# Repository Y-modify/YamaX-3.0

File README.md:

# YamaX 3.0

This is the software of humanoid robot named "YamaX 3.0"
The humanoid uses the original board with ESP8266.
This repository contains 3D Models, EAGLE files, and Arduino sketch.

Detailed information about this robot can be found in the following page: 

- [Y-modify](http://www.y-modify.org)
- [Y-modify Blog](http://blog.y-modify.org)

## Directory Structure

```
.
├── Designs
│   ├── AXBoard
│   │   ├── AX-03r	#EAGLE PCB file
│   │   └── Legacy	#Legacy Board (AX-03)
│   └── Model	#3D model of YamaX
├── Docs	#Document about the history of YamaX
└── Firmware
    └── AXBoard
        ├── AXTester	#Testing Program
        └── MCore	#Main Program
```

## Licence

These files are released under MIT Licence.
Please see `LICENCE`.

## Contact

You can comment on [our blog](http://blog.y-modify.org), or send e-mail to [info@y-modify.org](mailto:info@y-modify.org).

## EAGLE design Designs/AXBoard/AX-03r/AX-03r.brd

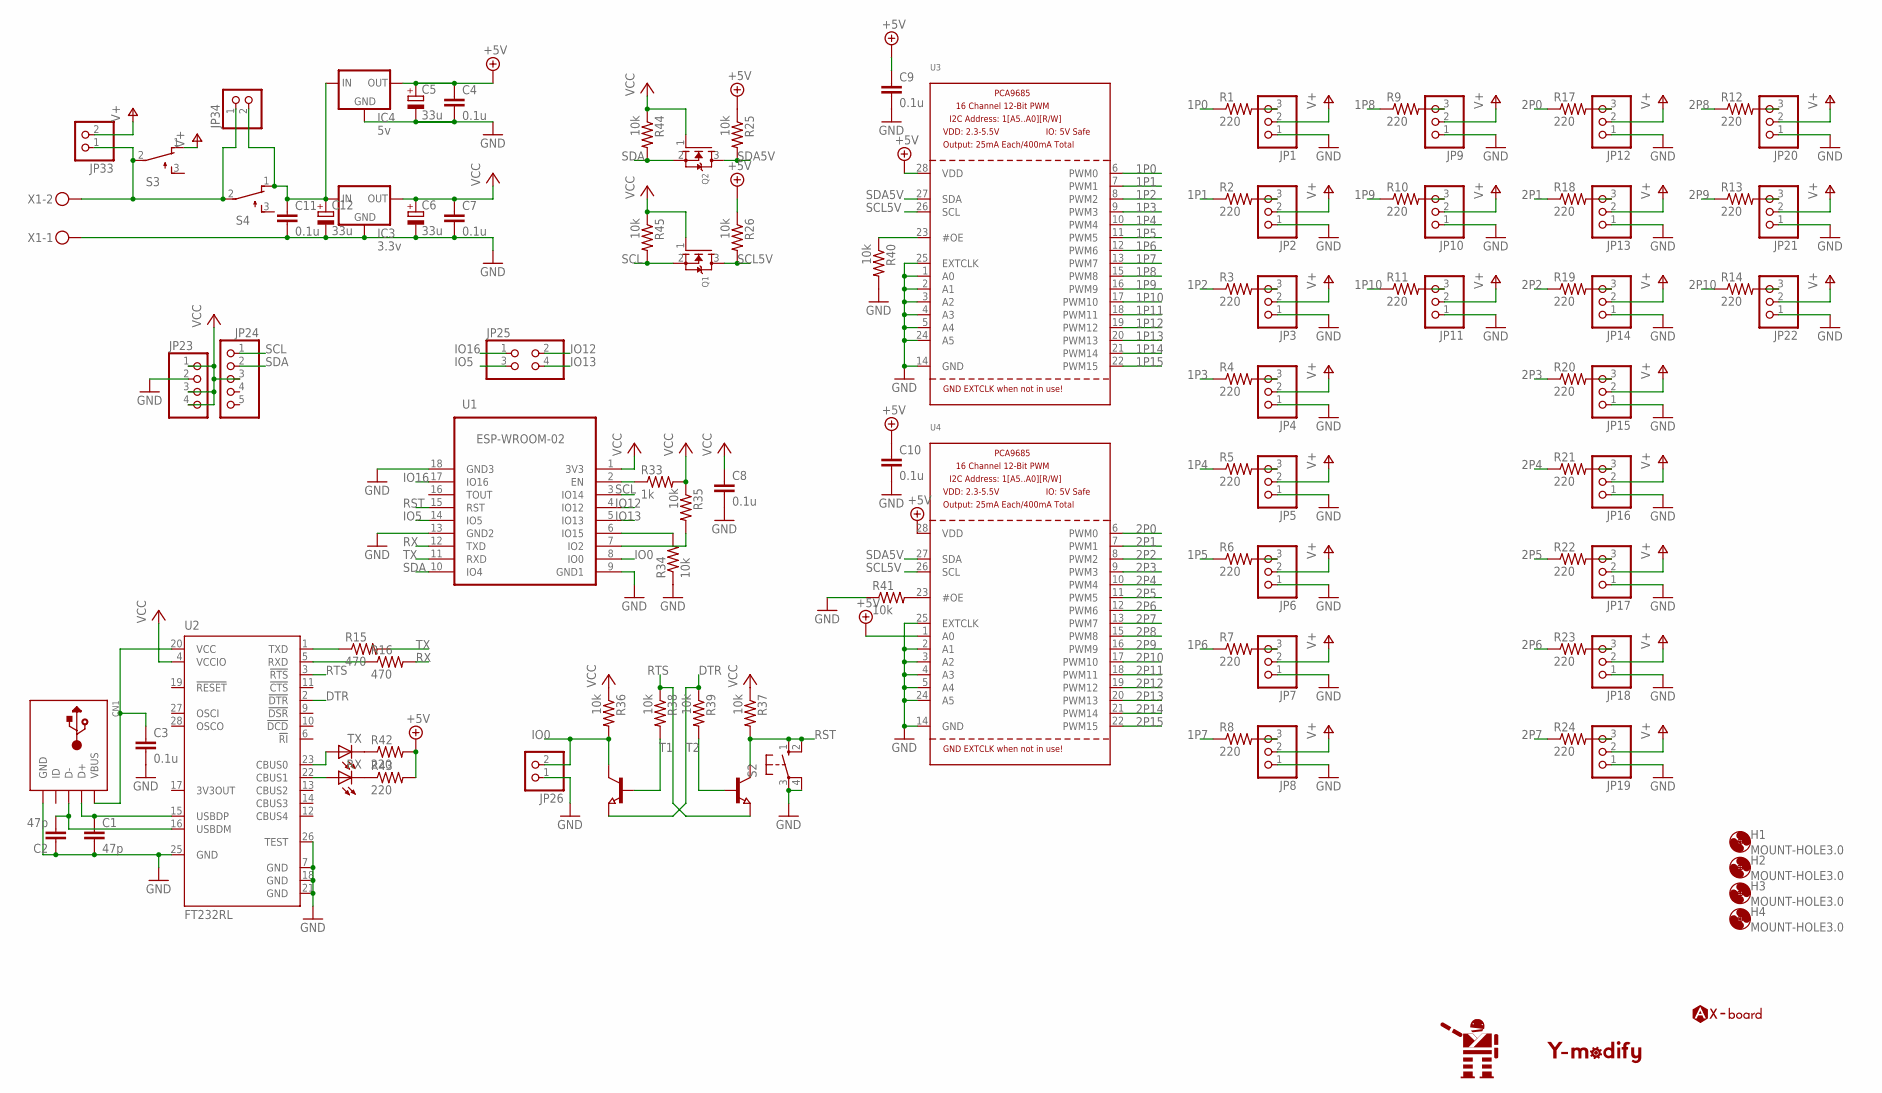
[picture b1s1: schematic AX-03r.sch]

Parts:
C1, C2: 47p; C025-025X050
C3, C4, C7, C8, C9, C10, C11: 0.1u; C025-025X050
C5, C6, C12: 33u; E2,5-6E
CN1: USBTHM; USB-MINIB-THM
H1, H2, H3, H4: MOUNT-HOLE3.0; 3,0
IC3: 3.3v; 78XXS
IC4: 5v; 78XXS
JP1, JP2, JP3, JP4, JP5, JP6, JP7, JP8, JP9, JP10, JP11, JP12, JP13, JP14, JP15, JP16, JP17, JP18, JP19, JP20, JP21, JP22: PINHD-1X3; 1X03
JP23: PINHD-1X4; 1X04
JP24: PINHD-1X5; 1X05
JP25: PINHD-2X2; 2X02
JP26, JP33, JP34: PINHD-1X2; 1X02
M1: MON
M2: Y-MODIFY
M3: AXBOARD
Q1, Q2: MOSFET-NWAVE; SOT23-W
R1, R2, R3, R4, R5, R6, R7, R8, R9, R10, R11, R12, R13, R14, R17, R18, R19, R20, R21, R22, R23, R24, R42, R43: 220; 0204V
R15, R16: 470; 0204V
R25, R26, R34, R35, R36, R37, R38, R39, R40, R41, R44, R45: 10k; 0204V
R33: 1k; 0204V
RX: LED3MM
S2: 10-XX; B3F-10XX
S3, S4: TL32PO; TL3XPO
T1, T2: NPN-TRANSISTOR_SOT23; SOT23
TX: LED3MM
U1: ESP-WROOM-02; FRONT-FACE
U2: FT232RL; SSOP28
U3, U4: PCA9685; TSSOP28
X1: MKDSN1,5/2-5,08

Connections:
1P0: R1.1, U3.6 (PWM0)
1P1: R2.1, U3.7 (PWM1)
1P2: R3.1, U3.8 (PWM2)
1P3: R4.1, U3.9 (PWM3)
1P4: R5.1, U3.10 (PWM4)
1P5: R6.1, U3.11 (PWM5)
1P6: R7.1, U3.12 (PWM6)
1P7: R8.1, U3.13 (PWM7)
1P8: R9.1, U3.15 (PWM8)
1P9: R10.1, U3.16 (PWM9)
1P10: R11.1, U3.17 (PWM10)
1P11: U3.18 (PWM11)
1P12: U3.19 (PWM12)
1P13: U3.20 (PWM13)
1P14: U3.21 (PWM14)
1P15: U3.22 (PWM15)
2P0: R17.1, U4.6 (PWM0)
2P1: R18.1, U4.7 (PWM1)
2P2: R19.1, U4.8 (PWM2)
2P3: R20.1, U4.9 (PWM3)
2P4: R21.1, U4.10 (PWM4)
2P5: R22.1, U4.11 (PWM5)
2P6: R23.1, U4.12 (PWM6)
2P7: R24.1, U4.13 (PWM7)
2P8: R12.1, U4.15 (PWM8)
2P9: R13.1, U4.16 (PWM9)
2P10: R14.1, U4.17 (PWM10)
2P11: U4.18 (PWM11)
2P12: U4.19 (PWM12)
2P13: U4.20 (PWM13)
2P14: U4.21 (PWM14)
2P15: U4.22 (PWM15)
+5V: C4.1, C5.+, C9.1, C10.1, IC4.OUT, R25.1, R26.1, R42.2, R43.2, U3.28 (VDD), U4.1 (A0), U4.28 (VDD)
DTR: R39.1, T1.2 (E), U2.2 (!DTR)
GND: C1.2, C2.1, C3.2, C4.2, C5.-, C6.-, C7.2, C8.2, C9.2, C10.2, C11.2, C12.-, CN1.GND, IC3.GND, IC4.GND, JP1.1, JP2.1, JP3.1, JP4.1, JP5.1, JP6.1, JP7.1, JP8.1, JP9.1, JP10.1, JP11.1, JP12.1, JP13.1, JP14.1, JP15.1, JP16.1, JP17.1, JP18.1, JP19.1, JP20.1, JP21.1, JP22.1, JP23.2, JP26.1, R34.1, R40.2, R41.1, S2.3, S2.4 (P1), U1.9 (GND1), U1.13 (GND2), U1.18 (GND3), U2.7 (GND), U2.18 (GND), U2.21 (GND), U2.25 (GND), U2.26 (TEST), U3.1 (A0), U3.2 (A1), U3.3 (A2), U3.4 (A3), U3.5 (A4), U3.14 (GND), U3.24 (A5), U3.25 (EXTCLK), U4.2 (A1), U4.3 (A2), U4.4 (A3), U4.5 (A4), U4.14 (GND), U4.24 (A5), U4.25 (EXTCLK), X1.1
IO0: JP26.2, R36.2, T1.3 (C), U1.8 (IO0)
IO5: JP25.3, U1.14 (IO5)
IO12: JP25.2, U1.4 (IO12)
IO13: JP25.4, U1.5 (IO13)
IO16: JP25.1, U1.17 (IO16)
unnamed: JP1.3, R1.2
unnamed: R33.1, U1.2 (EN)
unnamed: JP2.3, R2.2
unnamed: R34.2, U1.6 (IO15)
unnamed: JP3.3, R3.2
unnamed: R35.2, U1.7 (IO2)
unnamed: JP4.3, R4.2
unnamed: R41.2, U4.23 (#OE)
unnamed: JP5.3, R5.2
unnamed: R40.1, U3.23 (#OE)
unnamed: JP6.3, R6.2
unnamed: R38.2, T1.1 (B)
unnamed: JP7.3, R7.2
unnamed: R39.2, T2.1 (B)
unnamed: JP8.3, R8.2
unnamed: C1.1, CN1.D+, U2.15 (USBDP)
unnamed: JP9.3, R9.2
unnamed: JP10.3, R10.2
unnamed: JP11.3, R11.2
unnamed: JP20.3, R12.2
unnamed: JP21.3, R13.2
unnamed: JP22.3, R14.2
unnamed: C2.2, CN1.D-, U2.16 (USBDM)
unnamed: JP12.3, R17.2
unnamed: JP13.3, R18.2
unnamed: JP14.3, R19.2
unnamed: JP15.3, R20.2
unnamed: JP16.3, R21.2
unnamed: JP17.3, R22.2
unnamed: JP18.3, R23.2
unnamed: JP19.3, R24.2
unnamed: C3.1, CN1.VBUS, U2.20 (VCC)
unnamed: R42.1, TX.K (C)
unnamed: R43.1, RX.K (C)
unnamed: TX.A, U2.23 (CBUS0)
unnamed: RX.A, U2.22 (CBUS1)
unnamed: JP33.1, JP34.1, S3.2, S4.2, X1.2
unnamed: C11.1, C12.+, IC3.IN, IC4.IN, JP34.2, S4.1 (O)
unnamed: R15.1, U2.1 (TXD)
unnamed: R16.1, U2.5 (RXD)
RST: R37.2, S2.1 (S), S2.2 (S1), T2.3 (C), U1.15 (RST)
RTS: R38.1, T2.2 (E), U2.3 (!RTS)
RX: R16.2, U1.12 (TXD)
SCL: JP24.1, Q1.2 (S), R45.2, U1.3 (IO14)
SCL5V: Q1.3 (D), R26.2, U3.26 (SCL), U4.26 (SCL)
SDA: JP24.2, Q2.2 (S), R44.2, U1.10 (IO4)
SDA5V: Q2.3 (D), R25.2, U3.27 (SDA), U4.27 (SDA)
TX: R15.2, U1.11 (RXD)
V+: JP1.2, JP2.2, JP3.2, JP4.2, JP5.2, JP6.2, JP7.2, JP8.2, JP9.2, JP10.2, JP11.2, JP12.2, JP13.2, JP14.2, JP15.2, JP16.2, JP17.2, JP18.2, JP19.2, JP20.2, JP21.2, JP22.2, JP33.2, S3.1 (O)
VCC: C6.+, C7.1, C8.1, IC3.OUT, JP23.1, JP23.3, JP23.4, JP24.3, Q1.1 (G), Q2.1 (G), R33.2, R35.1, R36.1, R37.1, R44.1, R45.1, U1.1 (3V3), U2.4 (VCCIO)

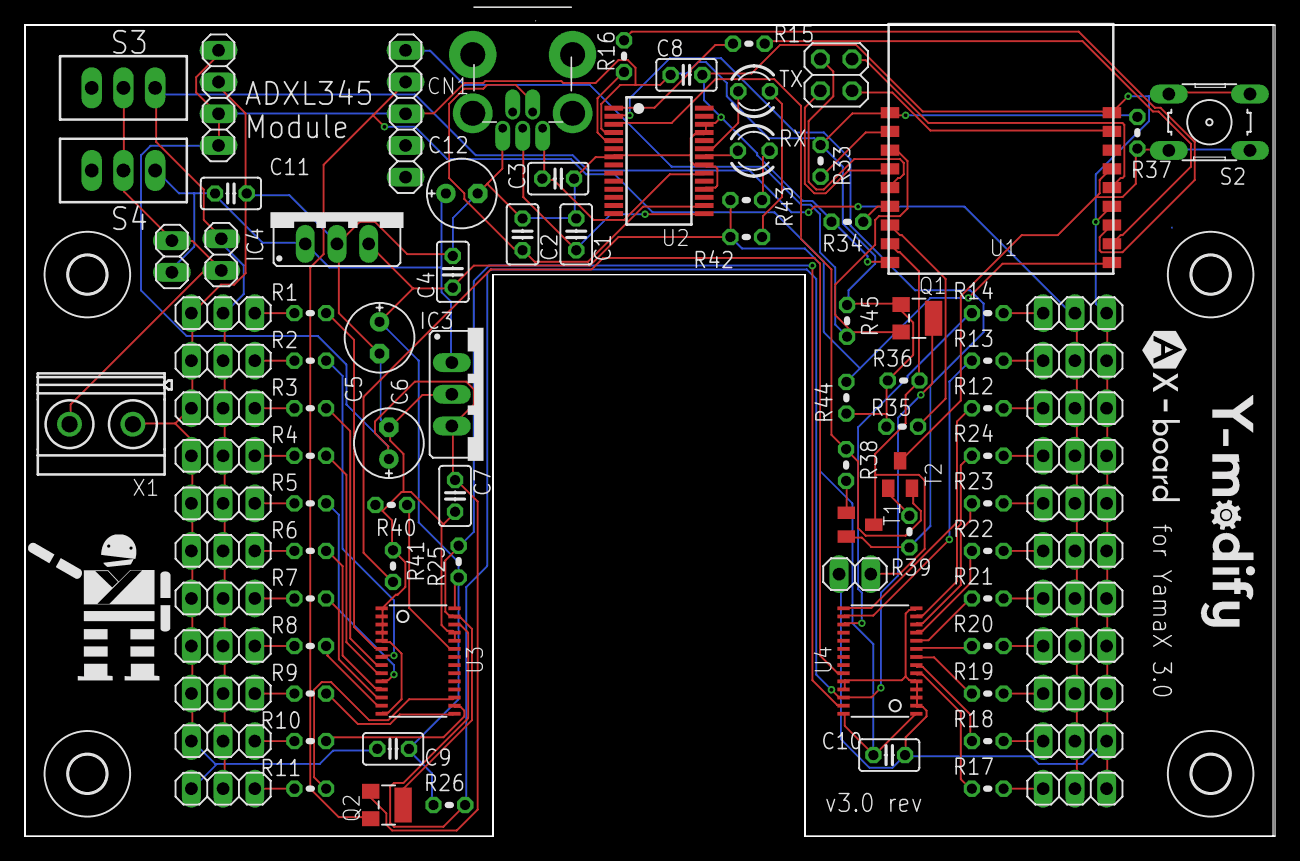
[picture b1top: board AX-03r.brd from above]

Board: 2 copper layers, 100.2 x 65.0 mm, 103 parts (0 on the bottom side), 80 nets.

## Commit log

2016-11-07 Initial Commit of YamaX 3.0
2016-11-07 Added LICENSE and README
2016-11-09 Translated Japanese comments into English
2016-11-09 Revert "Translated Japanese comments into English"
    This reverts commit a54f7284c32f948907b702977640837f4fbb292b.
2016-11-09 Revert "Revert "Translated Japanese comments into English""
    This reverts commit 1ec2eaea017d5ec38816b4111e9fea511e947f91.
2016-11-09 Fixed some words
